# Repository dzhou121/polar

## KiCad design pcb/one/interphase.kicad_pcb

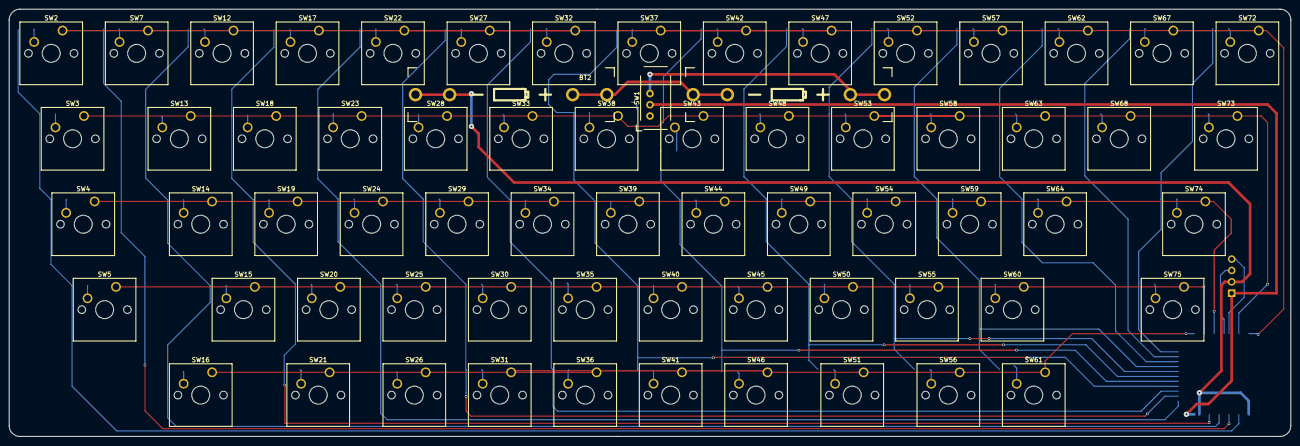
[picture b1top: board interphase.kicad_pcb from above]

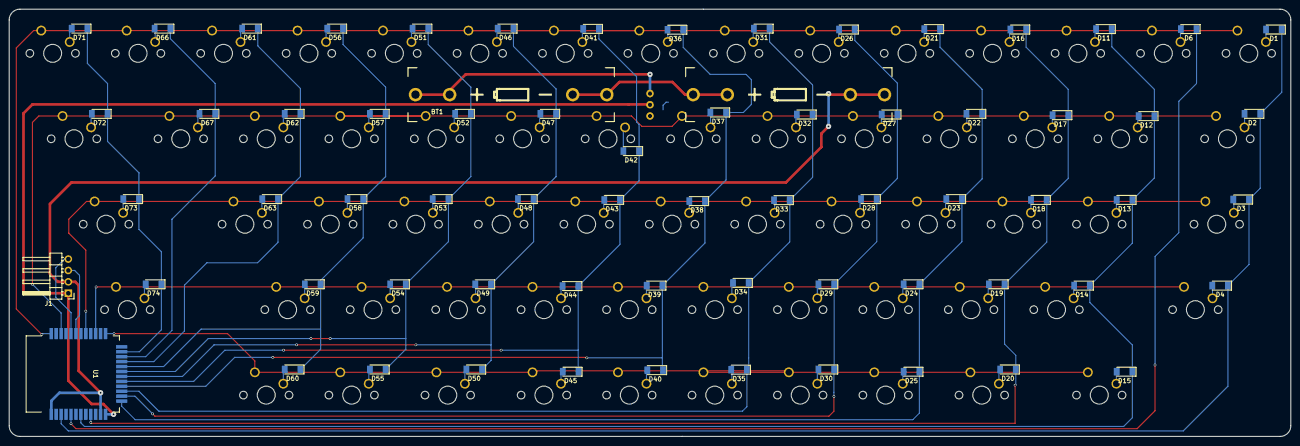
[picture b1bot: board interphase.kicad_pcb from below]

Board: 2 copper layers, 285.8 x 95.2 mm, 133 parts (67 on the bottom side), 90 nets.

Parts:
BT1, BT2: Battery_Cell; KEYSTONE-82_AAA_battery-clip
D1, D2, D3, D4, D6, D11, D12, D13, D14, D15, D16, D17, D18, D19, D20, D21, D22, D23, D24, D25, D26, D27, D28, D29, D30, D31, D32, D33, D34, D35, D36, D37, D38, D39, D40, D41, D42, D43, D44, D45, D46, D47, D48, D49, D50, D51, D52, D53, D54, D55, D56, D57, D58, D59, D60, D61, D62, D63, D66, D67, D71, D72, D73, D74: D; D_MiniMELF
J1: Conn_01x04_Male; Pin_Header_Angled_1x04_Pitch2.54mm
SW1: SW_SPDT; SW_E-Switch_EG1224_SPDT_Angled
SW2, SW7, SW12, SW13, SW14, SW15, SW17, SW18, SW19, SW20, SW22, SW23, SW24, SW25, SW26, SW27, SW28, SW29, SW30, SW31, SW32, SW33, SW34, SW35, SW36, SW37, SW38, SW39, SW40, SW41, SW42, SW43, SW44, SW45, SW46, SW47, SW48, SW49, SW50, SW52, SW53, SW54, SW55, SW56, SW57, SW58, SW59, SW60, SW61, SW62, SW63, SW64, SW67, SW68, SW72: MOM-SPST; SW_Cherry_MX1A_1.00u_PCB
SW3, SW16, SW73: MOM-SPST; SW_Cherry_MX1A_1.50u_PCB
SW4: MOM-SPST; SW_Cherry_MX1A_1.75u_PCB
SW5, SW74: MOM-SPST; SW_Cherry_MX1A_2.25u_PCB
SW21, SW51: MOM-SPST; SW_Cherry_MX1A_1.25u_PCB
SW75: MOM-SPST; SW_Cherry_MX1A_2.75u_PCB
U1: Core51822B; Core51822(B)

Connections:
+3V3: J1.1, SW1.2, U1.12
/col0: D1.1, D2.1, D3.1, D4.1, U1.3
/col1: D6.1, U1.5
/col2: D11.1, D12.1, D13.1, D14.1, D15.1, U1.7
/col3: D16.1, D17.1, D18.1, D19.1, D20.1, U1.9
/col4: D21.1, D22.1, D23.1, D24.1, D25.1, U1.13
/col5: D26.1, D27.1, D28.1, D29.1, D30.1, U1.14
/col6: D31.1, D32.1, D33.1, D34.1, D35.1, U1.15
/col7: D36.1, D37.1, D38.1, D39.1, D40.1, U1.16
/col8: D41.1, D42.1, D43.1, D44.1, D45.1, U1.17
/col9: D46.1, D47.1, D48.1, D49.1, D50.1, U1.18
/col10: D51.1, D52.1, D53.1, D54.1, D55.1, U1.19
/col11: D56.1, D57.1, D58.1, D59.1, D60.1, U1.20
/col12: D61.1, D62.1, D63.1, U1.21
/col13: D66.1, D67.1, U1.22
/col14: D71.1, D72.1, D73.1, D74.1, U1.23
/row0: SW2.1, SW7.1, SW12.1, SW17.1, SW22.1, SW27.1, SW32.1, SW37.1, SW42.1, SW47.1, SW52.1, SW57.1, SW62.1, SW67.1, SW72.1, U1.36
/row1: SW3.1, SW13.1, SW18.1, SW23.1, SW28.1, SW33.1, SW38.1, SW43.1, SW48.1, SW53.1, SW58.1, SW63.1, SW68.1, SW73.1, U1.34
/row2: SW4.1, SW14.1, SW19.1, SW24.1, SW29.1, SW34.1, SW39.1, SW44.1, SW49.1, SW54.1, SW59.1, SW64.1, SW74.1, U1.29
/row3: SW5.1, SW15.1, SW20.1, SW25.1, SW30.1, SW35.1, SW40.1, SW45.1, SW50.1, SW55.1, SW60.1, SW75.1, U1.27
/row4: SW16.1, SW21.1, SW26.1, SW31.1, SW36.1, SW41.1, SW46.1, SW51.1, SW56.1, SW61.1, U1.25
GND: BT2.2, J1.2, U1.1, U1.11
unnamed: BT1.1, SW1.3
unnamed: BT1.2, BT2.1
unnamed: D1.2, SW2.2
unnamed: D2.2, SW3.2
unnamed: D3.2, SW4.2
unnamed: D4.2, SW5.2
unnamed: D6.2, SW7.2
unnamed: D11.2, SW12.2
unnamed: D12.2, SW13.2
unnamed: D13.2, SW14.2
unnamed: D14.2, SW15.2
unnamed: D15.2, SW16.2
unnamed: D16.2, SW17.2
unnamed: D17.2, SW18.2
unnamed: D18.2, SW19.2
unnamed: D19.2, SW20.2
unnamed: D20.2, SW21.2
unnamed: D21.2, SW22.2
unnamed: D22.2, SW23.2
unnamed: D23.2, SW24.2
unnamed: D24.2, SW25.2
unnamed: D25.2, SW26.2
unnamed: D26.2, SW27.2
unnamed: D27.2, SW28.2
unnamed: D28.2, SW29.2
unnamed: D29.2, SW30.2
unnamed: D30.2, SW31.2
unnamed: D31.2, SW32.2
unnamed: D32.2, SW33.2
unnamed: D33.2, SW34.2
unnamed: D34.2, SW35.2
unnamed: D35.2, SW36.2
unnamed: D36.2, SW37.2
unnamed: D37.2, SW38.2
unnamed: D38.2, SW39.2
unnamed: D39.2, SW40.2
unnamed: D40.2, SW41.2
unnamed: D41.2, SW42.2
unnamed: D42.2, SW43.2
unnamed: D43.2, SW44.2
unnamed: D44.2, SW45.2
unnamed: D45.2, SW46.2
unnamed: D46.2, SW47.2
unnamed: D47.2, SW48.2
unnamed: D48.2, SW49.2
unnamed: D49.2, SW50.2
unnamed: D50.2, SW51.2
unnamed: D51.2, SW52.2
unnamed: D52.2, SW53.2
unnamed: D53.2, SW54.2
unnamed: D54.2, SW55.2
unnamed: D55.2, SW56.2
unnamed: D56.2, SW57.2
unnamed: D57.2, SW58.2
unnamed: D58.2, SW59.2
unnamed: D59.2, SW60.2
unnamed: D60.2, SW61.2
unnamed: D61.2, SW62.2
unnamed: D62.2, SW63.2
unnamed: D63.2, SW64.2
unnamed: D66.2, SW67.2
unnamed: D67.2, SW68.2
unnamed: D71.2, SW72.2
unnamed: D72.2, SW73.2
unnamed: D73.2, SW74.2
unnamed: D74.2, SW75.2
unnamed: J1.3, U1.31
unnamed: J1.4, U1.32

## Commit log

2018-04-18 change pcb
2018-04-18 ignore _build
2018-04-20 can send basic chars
2018-04-20 added firmware-right
2018-04-23 some changes
2018-04-23 left central enabled
2018-04-24 roughly working now
2018-04-24 add tmk support
2018-04-30 change to actual matrix
2018-04-30 code cleanup
2018-05-01 right update
2018-05-01 change keymap
2018-05-09 save previous work
2018-05-14 added firmware-main
2018-05-14 changes to firmware
2018-05-14 main and left roughly working
2018-05-15 timer working
2018-05-15 add gazll
2018-05-15 right timer
2018-05-15 change right program.sh
2018-05-15 uart flow control
2018-05-15 uart tuning
2018-05-17 firmware-one finish
2018-05-18 keymap change
2018-05-21 added bootmagic
2018-05-21 add sleep feature
2021-07-22 change gpio cfg
